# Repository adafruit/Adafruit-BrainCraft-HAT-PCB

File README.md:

## Adafruit Adafruit BrainCraft HAT - Machine Learning for Raspberry Pi 4 PCB

<a href="http://www.adafruit.com/products/4374"><br/>
Click here to purchase one from the Adafruit shop</a>

PCB files for the Adafruit BrainCraft HAT - Machine Learning for Raspberry Pi 4. 

Format is EagleCAD schematic and board layout
* https://www.adafruit.com/product/4374

### Description

The idea behind the BrainCraft HAT is that you’d be able to “craft brains” for Machine Learning on the EDGE, with Microcontrollers & Microcomputers. On ASK AN ENGINEER, our founder & engineer chatted with Pete Warden, the technical lead of the mobile, embedded TensorFlow Group on Google’s Brain team about what would be ideal for a board like this.

And here’s what we designed! The BrainCraft HAT has a 240×240 TFT IPS display for inference output, slots for camera connector cable for imaging projects, a 5 way joystick and button for UI input, left and right microphones, stereo headphone out, stereo 1 W speaker out, three RGB DotStar LEDs, two 3 pin STEMMA connectors on PWM pins so they can drive NeoPixels or servos, and Grove/STEMMA/Qwiic I2C port. This will let people build a wide range of audio/video AI projects while also allowing easy plug-in of sensors and robotics!

A controllable mini fan attaches to the bottom, and can be used to keep your Pi cool while doing intense AI inference calculations. **Most importantly, there’s an On/Off switch that will completely disable the audio codec, so that when it's off there’s no way it's listening to you.**

**Features:**
 * **1.54" IPS TFT** display with 240x240 resolution that can show text or video
 * **Stereo speaker ports for audio playback** - either text-to-speech, alerts or for creating a voice assistant.
 * **Stereo headphone out** for audio playback through a stereo system, headphones, or powered speakers.
 * **Stereo microphone input** - perfect for making your very own smart home assistants
 * **Two 3-pin JST STEMMA connectors** that can be used to [connect more buttons](https://www.adafruit.com/product/4431), [a relay](https://www.adafruit.com/product/4409), or [even some NeoPixels!](https://www.adafruit.com/product/3919)
 * **[STEMMA QT plug-and-play I2C port](https://learn.adafruit.com/introducing-adafruit-stemma-qt)**, can be used with [any of our 50+ I2C STEMMA QT boards](https://www.adafruit.com/category/620), or can be used to [connect to Grove I2C devices with an adapter cable](https://www.adafruit.com/product/4528).
 * **5-Way Joystick + Button** for user interface and control.
 * **Three RGB DotStar LEDs** for colorful LED feedback.

The STEMMA QT port means you can attach heat image sensors like the [Panasonic Grid-EYE](https://www.adafruit.com/product/3538) or [MLX90640](https://www.adafruit.com/?q=mlx90640&sort=BestMatch). Heat-Sensitive cameras can be used as a person detector, even in the dark! An external accelerometer can be attached for gesture or vibration sensing such as machinery/industrial predictive maintenance projects

### License

Adafruit invests time and resources providing this open source design, please support Adafruit and open-source hardware by purchasing products from [Adafruit](https://www.adafruit.com)!

Designed by Limor Fried/Ladyada for Adafruit Industries.

Creative Commons Attribution/Share-Alike, all text above must be included in any redistribution. 
See license.txt for additional details.

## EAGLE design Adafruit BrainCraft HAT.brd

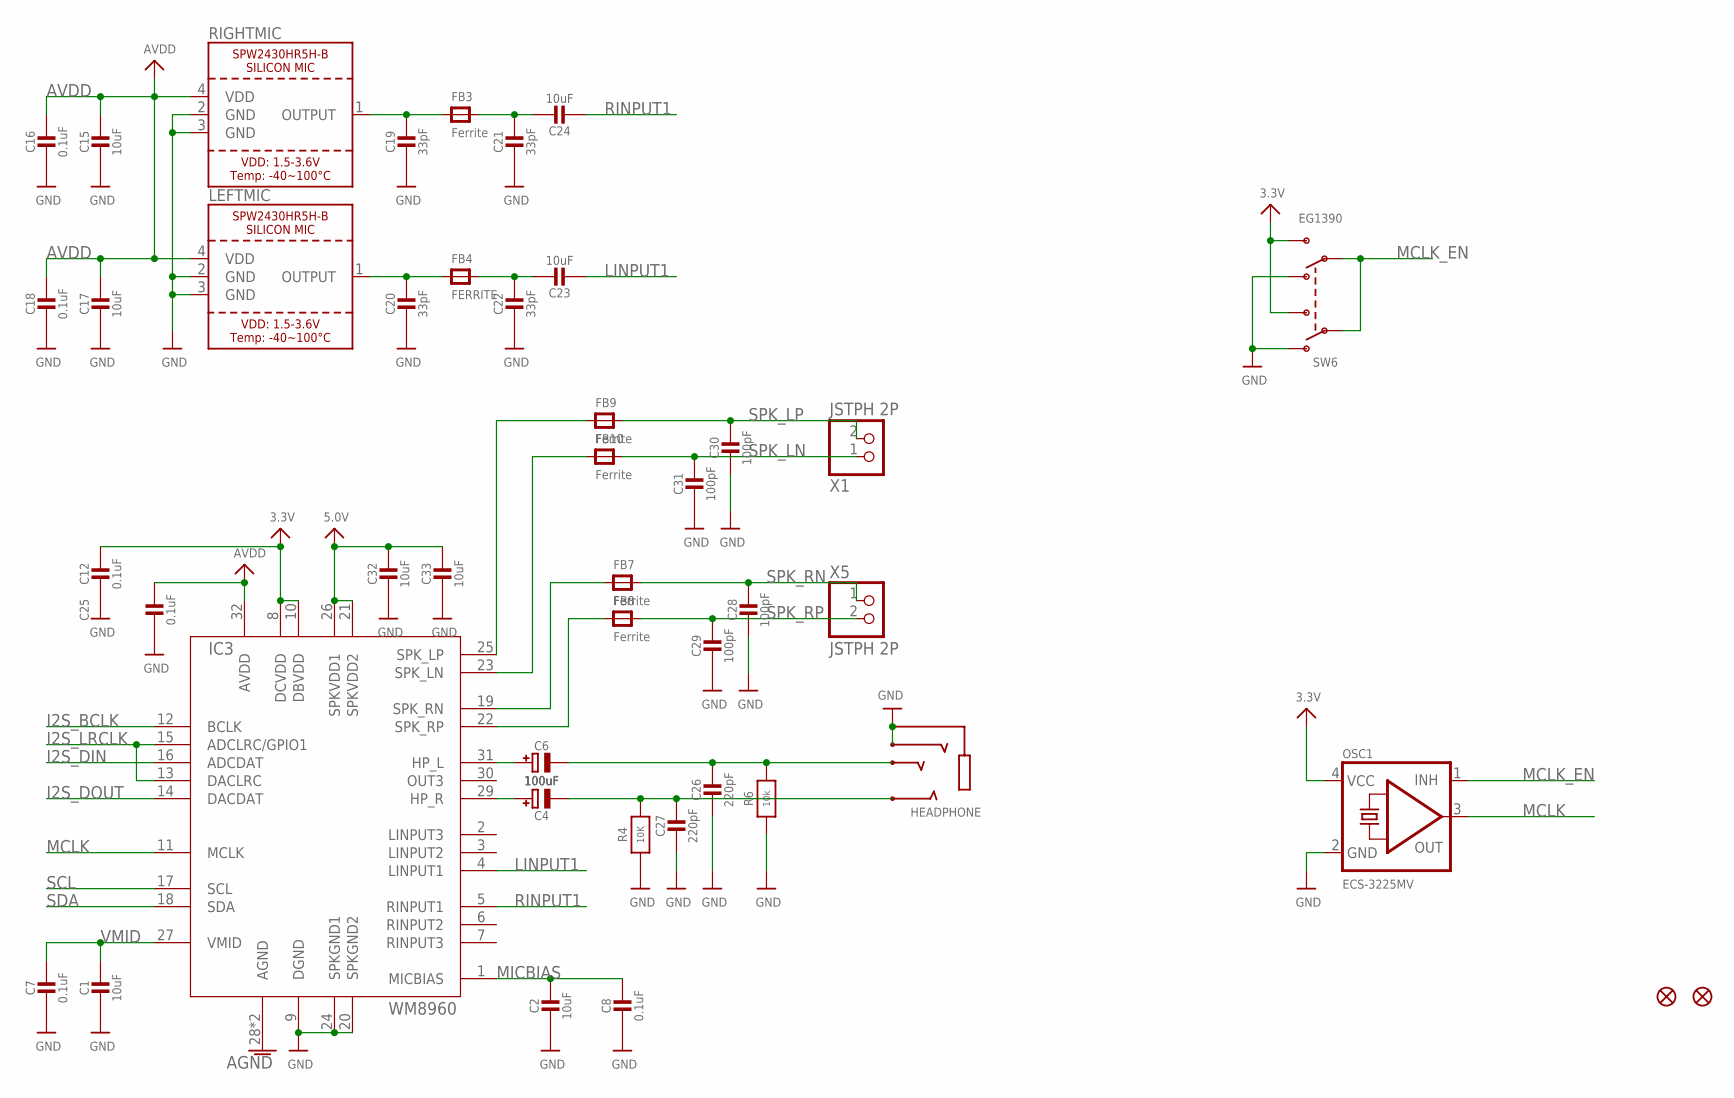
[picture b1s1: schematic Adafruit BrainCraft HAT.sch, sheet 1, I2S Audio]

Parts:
C1, C2, C15, C17, C23, C24, C32, C33: 10uF; 0805-NO
C4, C6: 100uF; PANASONIC_C
C7, C8, C12, C16, C18, C25: 0.1uF; 0603-NO
C19, C20, C21, C22: 33pF; 0603-NO
C26, C27: 220pF; 0603-NO
C28, C29, C30, C31: 100pF; 0603-NO
FB3, FB7, FB8, FB9, FB10: Ferrite; 0805-NO
FB4: FERRITE; 0805-NO
FID1, FID2: FIDUCIAL_1MM
HEADPHONE: AUDIO_3.5MMJACK_4POL; 4UCONN_18510
IC3: WM8960; QFN32_5MM
LEFTMIC: SPW2430HR5H-B
OSC1: ECS-3225MV; OSC_3.2X2.5MM
R4: 10K; 0603-NO
R6: 10k; 0603-NO
RIGHTMIC: SPW2430HR5H-B
SW6: EG1390
X1, X5: JSTPH 2P; JSTPH2

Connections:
3.3V: C12.1, IC3.8 (DCVDD), IC3.10 (DBVDD), OSC1.4 (VCC), SW6.S1, SW6.S2; also elsewhere on the board
5.0V: C32.1, C33.1, IC3.21 (SPKVDD2), IC3.26 (SPKVDD1); also elsewhere on the board
AGND: IC3.28 (AGND), IC3.33 (AGND); also elsewhere on the board
AVDD: C15.1, C16.1, C17.1, C18.1, C25.1, IC3.32 (AVDD), LEFTMIC.4 (VDD), RIGHTMIC.4 (VDD); also elsewhere on the board
GND: C1.2, C2.2, C7.2, C8.2, C12.2, C15.2, C16.2, C17.2, C18.2, C19.2, C20.2, C21.2, C22.2, C25.2, C26.2, C27.2, C28.2, C29.2, C30.2, C31.2, C32.2, C33.2, HEADPHONE.1-GND (TIP), HEADPHONE.4-INNER_SLEEVE (RING1), IC3.9 (DGND), IC3.20 (SPKGND2), IC3.24 (SPKGND1), LEFTMIC.2 (GND), LEFTMIC.3 (GND), OSC1.2 (GND), R4.1, R6.1, RIGHTMIC.2 (GND), RIGHTMIC.3 (GND), SW6.O1, SW6.O2; also elsewhere on the board
I2S_BCLK: IC3.12 (BCLK); also elsewhere on the board
I2S_DIN: IC3.16 (ADCDAT); also elsewhere on the board
I2S_DOUT: IC3.14 (DACDAT); also elsewhere on the board
I2S_LRCLK: IC3.13 (DACLRC), IC3.15 (ADCLRC/GPIO1); also elsewhere on the board
LINPUT1: C23.2, IC3.4 (LINPUT1)
MCLK: IC3.11 (MCLK), OSC1.3 (OUT)
MCLK_EN: OSC1.1 (INH), SW6.P1, SW6.P2
MICBIAS: C2.1, C8.1, IC3.1 (MICBIAS)
unnamed: FB7.1, IC3.19 (SPK_RN)
unnamed: FB8.1, IC3.22 (SPK_RP)
unnamed: C6.+, IC3.31 (HP_L)
unnamed: C4.+, IC3.29 (HP_R)
unnamed: C4.-, C27.1, HEADPHONE.3-OUTER_SLEEVE (RING2), R4.2
unnamed: C6.-, C26.1, HEADPHONE.2-TIP (RING3), R6.2
unnamed: C19.1, FB3.1, RIGHTMIC.1 (OUTPUT)
unnamed: C20.1, FB4.1, LEFTMIC.1 (OUTPUT)
unnamed: C21.1, C24.1, FB3.2
unnamed: C22.1, C23.1, FB4.2
unnamed: FB9.1, IC3.25 (SPK_LP)
unnamed: FB10.1, IC3.23 (SPK_LN)
RINPUT1: C24.2, IC3.5 (RINPUT1)
SCL: IC3.17 (SCL); also elsewhere on the board
SDA: IC3.18 (SDA); also elsewhere on the board
SPK_LN: C31.1, FB10.2, X1.1
SPK_LP: C30.1, FB9.2, X1.2
SPK_RN: C28.1, FB7.2, X5.1
SPK_RP: C29.1, FB8.2, X5.2
VMID: C1.1, C7.1, IC3.27 (VMID)

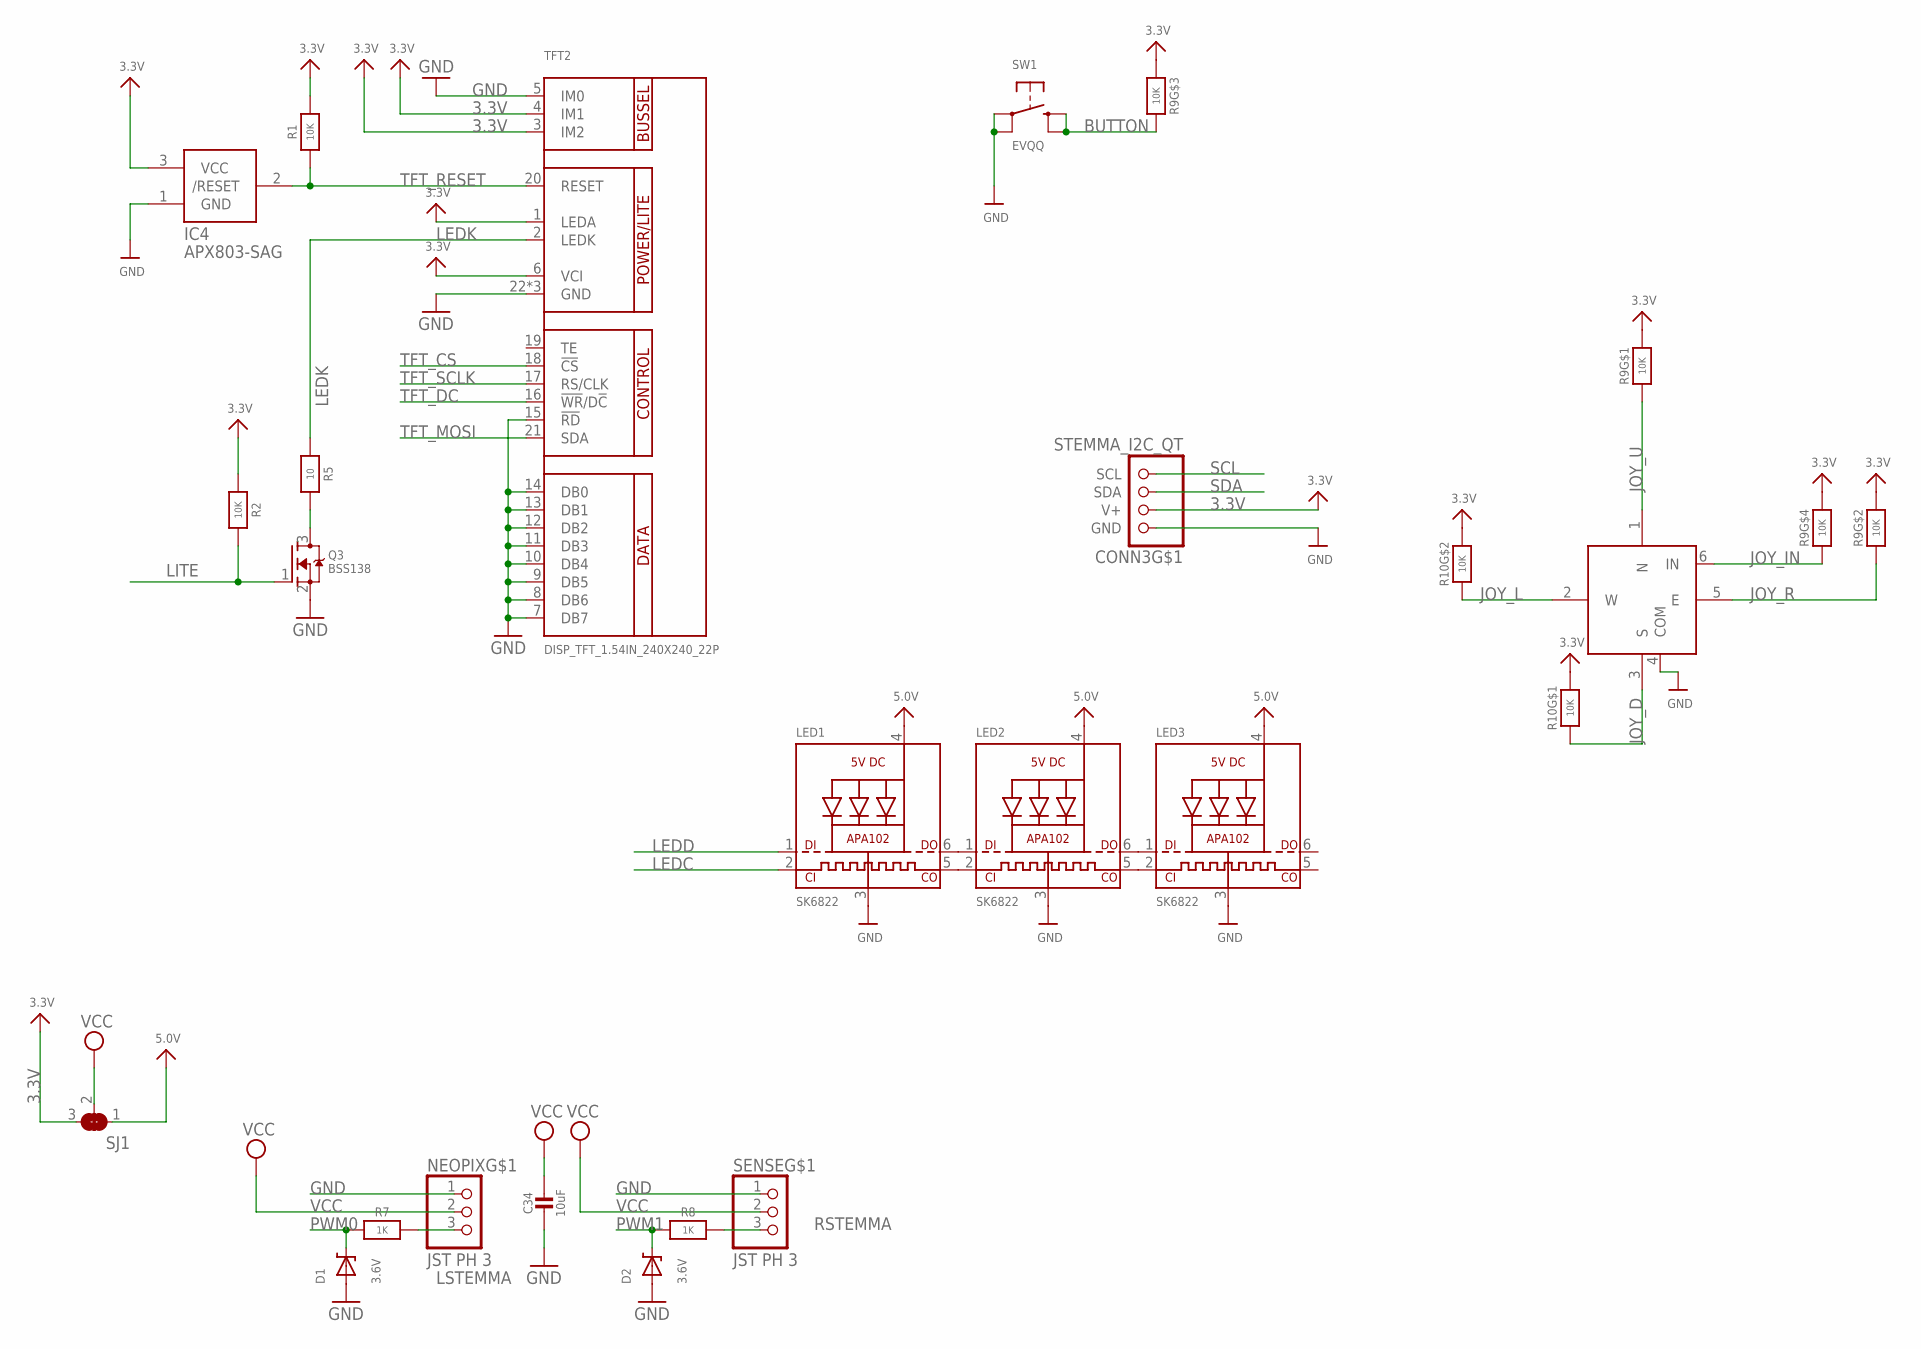
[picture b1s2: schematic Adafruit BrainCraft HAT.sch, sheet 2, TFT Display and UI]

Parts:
C34: 10uF; 0805-NO
CONN3: STEMMA_I2C_QT; JST_SH4
D1, D2: 3.6V; SOD-323
IC4: APX803-SAG; SOT23
LED1, LED2, LED3: SK6822; APA102
NEOPIX: JST PH 3; JSTPH3
Q3: BSS138; SOT23-WIDE
R1, R2: 10K; 0603-NO
R5: 10; 0603-NO
R7, R8: 1K; 0603-NO
R9, R10: 10K; RESPACK_4X0603
SENSE: JST PH 3; JSTPH3
SJ1: SOLDERJUMPER_2WAY; SOLDERJUMPER_2WAY_OPEN_NOPASTE
SW1: EVQQ; EVQ-Q2_SMALLER
SW5: NAVSWITCHSKQUABAUE010; SKQUBAE010
TFT2: DISP_TFT_1.54IN_240X240_22P; TFT_1.54IN_240X240_22PIN

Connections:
3.3V: CONN3.2 (V+), IC4.3 (VCC), R1.2, R2.2, R9.5 (2), R9.6 (2), R9.7 (2), R9.8 (2), R10.7 (2), R10.8 (2), SJ1.3, TFT2.1 (LEDA), TFT2.3 (IM2), TFT2.4 (IM1), TFT2.6 (VCI); also elsewhere on the board
5.0V: LED1.4 (VDD), LED2.4 (VDD), LED3.4 (VDD), SJ1.1; also elsewhere on the board
BUTTON: R9.3 (1), SW1.B (S), SW1.B' (S1); also elsewhere on the board
GND: C34.2, CONN3.1 (GND), D1.A, D2.A, IC4.1 (GND), LED1.3 (GND), LED2.3 (GND), LED3.3 (GND), NEOPIX.1, Q3.2 (S), SENSE.1, SW1.A, SW1.A' (P1), SW5.4 (COM), TFT2.5 (IM0), TFT2.7 (DB7), TFT2.8 (DB6), TFT2.9 (DB5), TFT2.10 (DB4), TFT2.11 (DB3), TFT2.12 (DB2), TFT2.13 (DB1), TFT2.14 (DB0), TFT2.15 (!RD), TFT2.22 (GND), TFT2.SUPPORT1 (GND), TFT2.SUPPORT2 (GND); also elsewhere on the board
JOY_D: R10.1, SW5.3 (S); also elsewhere on the board
JOY_IN: R9.4 (1), SW5.6 (IN); also elsewhere on the board
JOY_L: R10.2 (1), SW5.2 (W); also elsewhere on the board
JOY_R: R9.2 (1), SW5.5 (E); also elsewhere on the board
JOY_U: R9.1, SW5.1 (N); also elsewhere on the board
LEDC: LED1.2 (CKI); also elsewhere on the board
LEDD: LED1.1 (DI); also elsewhere on the board
LEDK: R5.2, TFT2.2 (LEDK)
LITE: Q3.1 (G), R2.1; also elsewhere on the board
LSTEMMA: NEOPIX.3, R7.1
unnamed: Q3.3 (D), R5.1
unnamed: LED1.6 (DO), LED2.1 (DI)
unnamed: LED1.5 (CKO), LED2.2 (CKI)
unnamed: LED2.6 (DO), LED3.1 (DI)
unnamed: LED2.5 (CKO), LED3.2 (CKI)
PWM0: D1.C, R7.2; also elsewhere on the board
PWM1: D2.C, R8.2; also elsewhere on the board
RSTEMMA: R8.1, SENSE.3
SCL: CONN3.4 (SCL); also elsewhere on the board
SDA: CONN3.3 (SDA); also elsewhere on the board
TFT_CS: TFT2.18 (!CS); also elsewhere on the board
TFT_DC: TFT2.16 (!WR!/D!C); also elsewhere on the board
TFT_MOSI: TFT2.21 (SDA); also elsewhere on the board
TFT_RESET: IC4.2 (/RESET), R1.1, TFT2.20 (RESET)
TFT_SCLK: TFT2.17 (RS/CLK); also elsewhere on the board
VCC: C34.1, NEOPIX.2, SENSE.2, SJ1.2

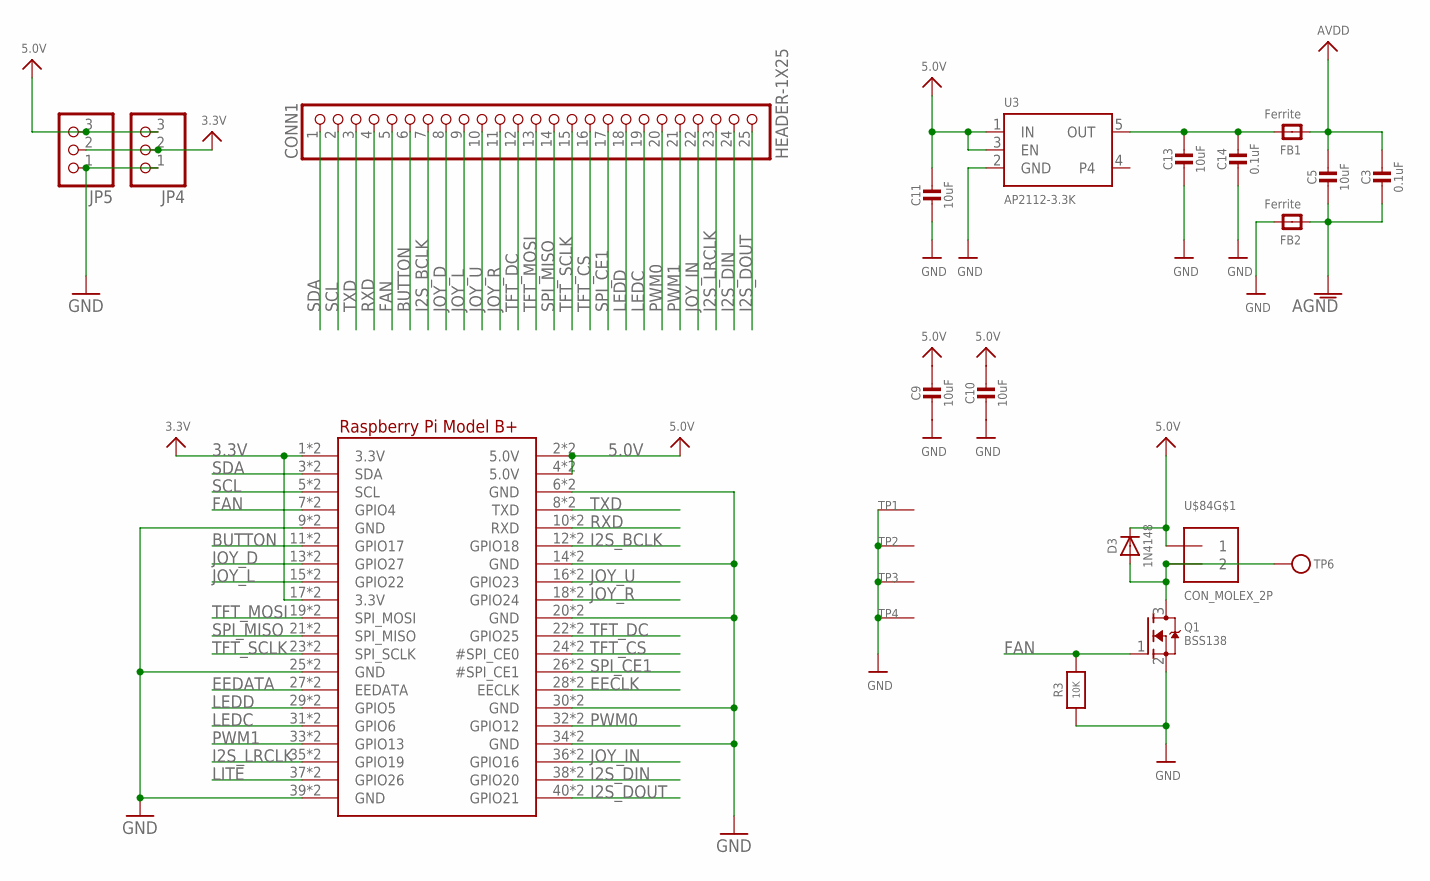
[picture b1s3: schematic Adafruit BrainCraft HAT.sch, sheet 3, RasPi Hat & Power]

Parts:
C3, C14: 0.1uF; 0603-NO
C5, C9, C10, C11, C13: 10uF; 0805-NO
CONN1: HEADER-1X25; 1X25_ROUND_70MIL
D3: 1N4148; SOD-323
FB1, FB2: Ferrite; 0805
JP4, JP5: HEADER-1X376MIL; 1X03_ROUND_76
Q1: BSS138; SOT23-WIDE
R3: 10K; 0603-NO
RPI1: RASPBERRYPI_BPLUS_HAT_SMTTHM_SLOTS; PI_HAT_SMTTHM_SLOTS
TP1, TP2, TP3, TP4: SEWTAP_SMTNUTM3; SMT_NUT_3MM
TP6: TESTPOINTROUND2MM; TESTPOINT_ROUND_2MM
U3: AP2112-3.3K; SOT23-5
U$84: CON_MOLEX_2P; 53398-0271

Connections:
3.3V: JP4.2, JP5.2, RPI1.1 (3.3V), RPI1.17 (3.3V), RPI1.S1 (3.3V), RPI1.S17 (3.3V); also elsewhere on the board
5.0V: C9.1, C10.1, C11.1, D3.C, JP4.3, JP5.3, RPI1.2 (5.0V), RPI1.4 (5.0V), RPI1.S2 (5.0V), RPI1.S4 (5.0V), U3.1 (IN), U3.3 (EN), U$84.1; also elsewhere on the board
AGND: C3.2, C5.2, FB2.1; also elsewhere on the board
AVDD: C3.1, C5.1, FB1.1; also elsewhere on the board
BUTTON: CONN1.6, RPI1.11 (GPIO17), RPI1.S11 (GPIO17); also elsewhere on the board
EECLK: RPI1.28 (EECLK), RPI1.S28 (EECLK)
EEDATA: RPI1.27 (EEDATA), RPI1.S27 (EEDATA)
FAN: CONN1.5, Q1.1 (G), R3.1, RPI1.7 (GPIO4), RPI1.S7 (GPIO4)
GND: C9.2, C10.2, C11.2, C13.2, C14.2, FB2.2, JP4.1, JP5.1, Q1.2 (S), R3.2, RPI1.6 (GND), RPI1.9 (GND), RPI1.14 (GND), RPI1.20 (GND), RPI1.25 (GND), RPI1.30 (GND), RPI1.34 (GND), RPI1.39 (GND), RPI1.S6 (GND), RPI1.S9 (GND), RPI1.S14 (GND), RPI1.S20 (GND), RPI1.S25 (GND), RPI1.S30 (GND), RPI1.S34 (GND), RPI1.S39 (GND), TP1.P$1, TP2.P$1, TP3.P$1, TP4.P$1, U3.2 (GND); also elsewhere on the board
I2S_BCLK: CONN1.7, RPI1.12 (GPIO18), RPI1.S12 (GPIO18); also elsewhere on the board
I2S_DIN: CONN1.24, RPI1.38 (GPIO20), RPI1.S38 (GPIO20); also elsewhere on the board
I2S_DOUT: CONN1.25, RPI1.40 (GPIO21), RPI1.S40 (GPIO21); also elsewhere on the board
I2S_LRCLK: CONN1.23, RPI1.35 (GPIO19), RPI1.S35 (GPIO19); also elsewhere on the board
JOY_D: CONN1.8, RPI1.13 (GPIO27), RPI1.S13 (GPIO27); also elsewhere on the board
JOY_IN: CONN1.22, RPI1.36 (GPIO16), RPI1.S36 (GPIO16); also elsewhere on the board
JOY_L: CONN1.9, RPI1.15 (GPIO22), RPI1.S15 (GPIO22); also elsewhere on the board
JOY_R: CONN1.11, RPI1.18 (GPIO24), RPI1.S18 (GPIO24); also elsewhere on the board
JOY_U: CONN1.10, RPI1.16 (GPIO23), RPI1.S16 (GPIO23); also elsewhere on the board
LEDC: CONN1.19, RPI1.31 (GPIO6), RPI1.S31 (GPIO6); also elsewhere on the board
LEDD: CONN1.18, RPI1.29 (GPIO5), RPI1.S29 (GPIO5); also elsewhere on the board
LITE: RPI1.37 (GPIO26), RPI1.S37 (GPIO26); also elsewhere on the board
unnamed: D3.A, Q1.3 (D), TP6.P$1, U$84.2
OUT: C13.1, C14.1, FB1.2, U3.5 (OUT)
PWM0: CONN1.20, RPI1.32 (GPIO12), RPI1.S32 (GPIO12); also elsewhere on the board
PWM1: CONN1.21, RPI1.33 (GPIO13), RPI1.S33 (GPIO13); also elsewhere on the board
RXD: CONN1.4, RPI1.10 (RXD), RPI1.S10 (RXD)
SCL: CONN1.2, RPI1.5 (SCL), RPI1.S5 (SCL); also elsewhere on the board
SDA: CONN1.1, RPI1.3 (SDA), RPI1.S3 (SDA); also elsewhere on the board
SPI_CE1: CONN1.17, RPI1.26 (#SPI_CE1), RPI1.S26 (#SPI_CE1)
SPI_MISO: CONN1.14, RPI1.21 (SPI_MISO), RPI1.S21 (SPI_MISO)
TFT_CS: CONN1.16, RPI1.24 (#SPI_CE0), RPI1.S24 (#SPI_CE0); also elsewhere on the board
TFT_DC: CONN1.12, RPI1.22 (GPIO25), RPI1.S22 (GPIO25); also elsewhere on the board
TFT_MOSI: CONN1.13, RPI1.19 (SPI_MOSI), RPI1.S19 (SPI_MOSI); also elsewhere on the board
TFT_SCLK: CONN1.15, RPI1.23 (SPI_SCLK), RPI1.S23 (SPI_SCLK); also elsewhere on the board
TXD: CONN1.3, RPI1.8 (TXD), RPI1.S8 (TXD)

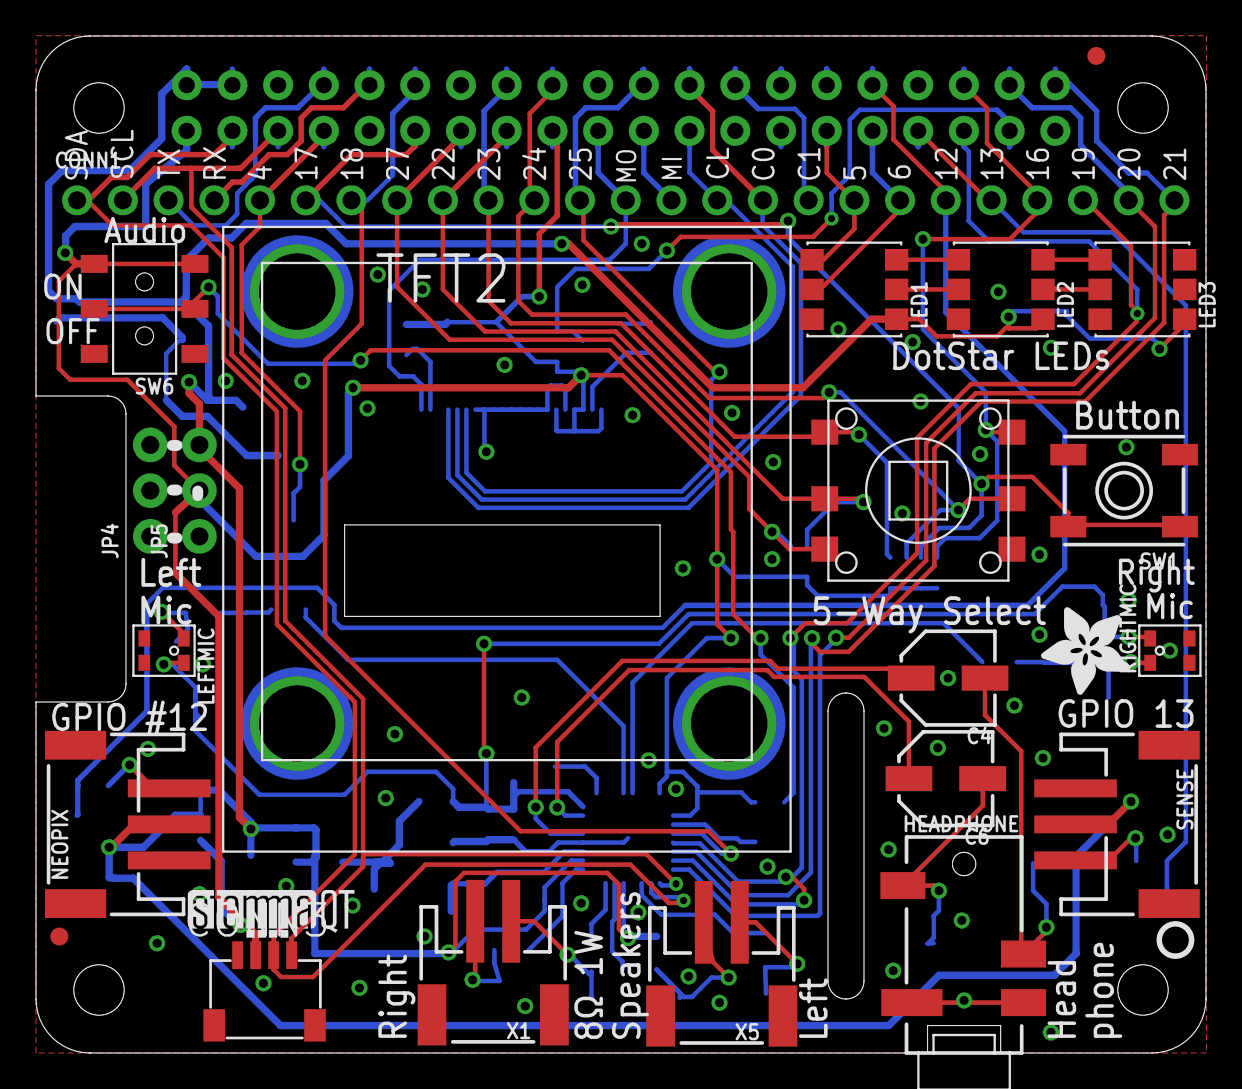
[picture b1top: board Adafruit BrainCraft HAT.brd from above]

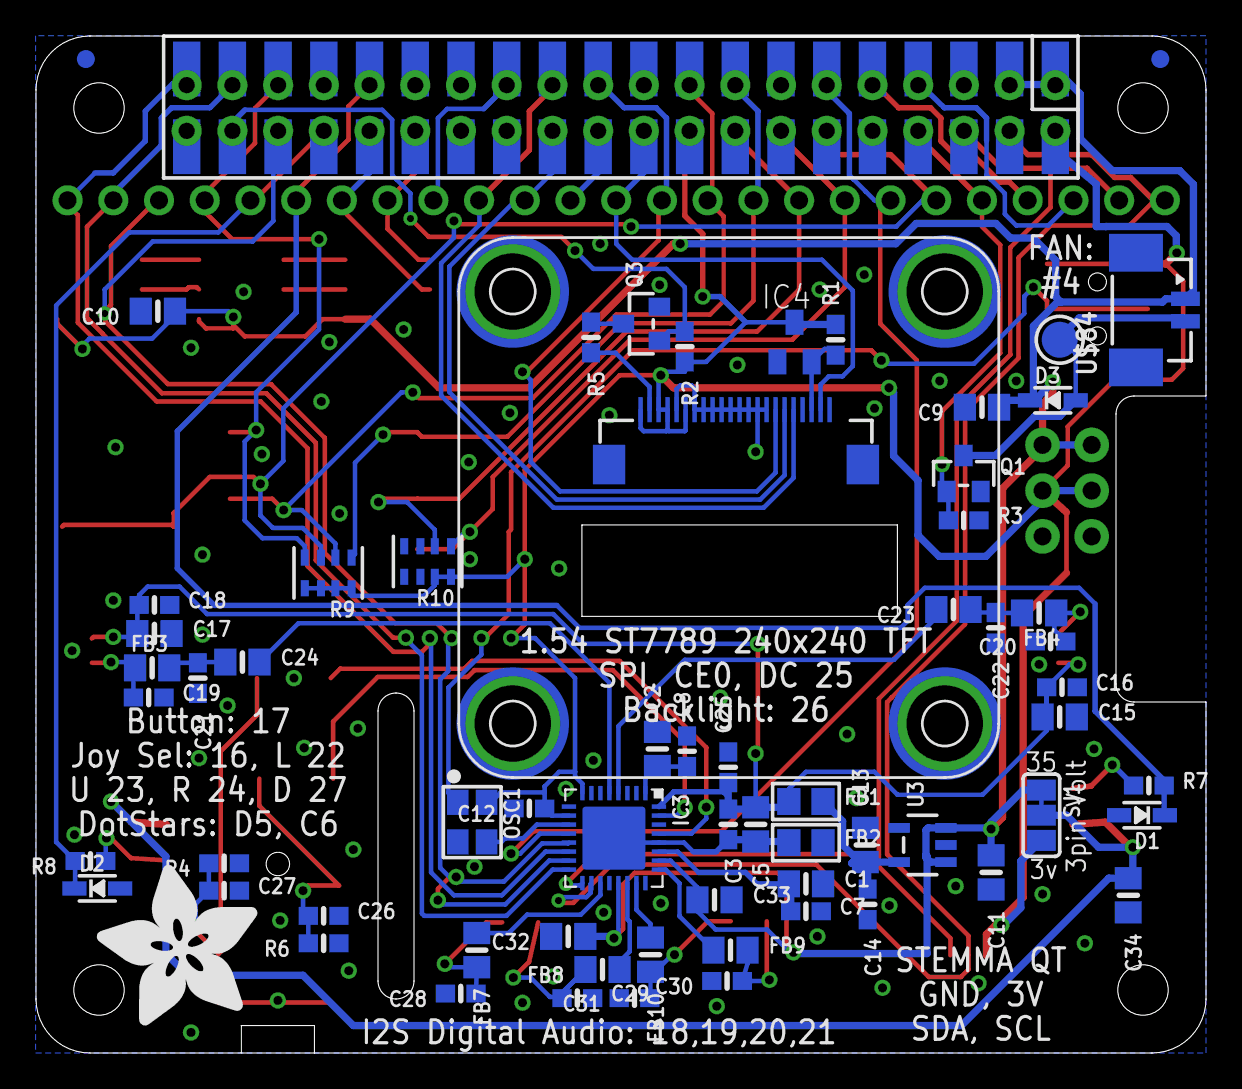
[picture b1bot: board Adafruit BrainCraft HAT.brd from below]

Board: 2 copper layers, 65.0 x 56.5 mm, 95 parts (69 on the bottom side), 67 nets.

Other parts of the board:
U$11: PCBFEAT-REV-040
U$72: STEMMAQT
U$75: ADAFRUIT_5MM
U$79: BRAINPAD_1IN
U$82: FAN_30X30MM
U$87: ADAFRUIT_9MM

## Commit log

2020-10-05 Added files

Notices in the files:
parts and their libraries:
microbuilder: This work is placed in the public domain, and may be freely used for commercial and non-commercial work with the following conditions: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
